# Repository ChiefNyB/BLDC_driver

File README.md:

# BLDC driver
 [TI DRV10983-Q1](https://www.ti.com/product/DRV10983-Q1/) based BLDC motor controller

 Development software: KiCad 8.0.5 (latest)

 ## *Üzenet*

 Szerintem majd ide a README-be írogathatjuk dokumnetáció vázlatos részét,
 a számítást meg Excelbe vagy valami python scriptbe lehet nyomni
 (ugyanígy version controllozva), aztán innen aztán mehet majd Word-be a bővebb leírás.

 Éés szerintem nyugodtan írogathatunk ide kommenteket is, talán kevésbé veszik
 el mint a chatben.

 Légyszi nézzétek meg a katalógust is (bent van a datasheet mappában), meg az áramkört is,
 igyekeztem leírni a dolgokat amiket csináltam. Mindezek alapján remélem, hogy nektek is érthető lesz majd, hogy mi mit csinál.
 Ha bármi kérdésetek van, írjátok akár ide valahova, akár messengeren. Légyszi mindketten olvassátok el az egész README-t!
 Köszi :)

 Ide kigyűjtöttem, hogy szerintem még mi kell:

 ## További lépések (nagy vonalakban)

  - Komponensek értékeinek kiszámítása --> komponensek választása
  - Fizikai layout kialakítása
  - (adhatnánk majd a hozzá passzoló motorokra egy példát)

## Dokumentáció vázlatosan (kapcsolás)
(ömlesztett gondolatok, egy csöppet össze-vissza)

KORREKCIÓ: A TVS DIÓDÁT EGYENLŐRE KISZEDTEM, VAN BEÉPÍTETT A CHIPBE
  
  - a chip modellt (footprint, stb...) a
  TI-os lapról töltöttem és illesztettem be: [link](https://vendor.ultralibrarian.com/TI/embedded/?gpn=DRV10983-Q1&package=PWP&pin=24&sid=&c=0)
  (lementettem saját global libraryba... ha nektek valami miatt nem látszódna, akkor
  ezt lehet nektek is meg kell csinálni)
  - IC bekötése a datasheet 64. oldalán található 71.figureban, egy csomó komponens (főleg kondik) értéke innen van
  található kapcsolás alapján (lehet arról írni esetleg, hogy milyen funkciói vannak
  az IC-nek)
    - 12Vról megy, (esetleg 24V, de ha 28-ig visszatölt, akkor már egyébként lekapcsolja a powerstaget)
    - I2C max 400kHz
    - milyen lekapcsolási-biztonsági funkciók vannak (Over voltage, o.current, thermal shutdown...)
  - a schematic hierarhikus, több lapból áll (drive, power), de nem is biztos hogy szükség lenne rá, mert elég egyszerű,
  csak kicsit fancybb és esetleg segíti a logikát átlátni
  - a pontos típus: [DRV10983SQ](https://www.ti.com/product/DRV10983-Q1/part-details/DRV10983SQPWPRQ1) legyen, ha standby modeban is 
  használni szeretnénk az 5V-os buck convertert --> mikrovezérlő meghajtható róla (ld. katalógus 3.o.)
  - I2C védelmet és szűrést [ez](https://www.we-online.com/components/media/o734709v410%20ANP121a%20%20Filter%20and%20surge%20protection%20for%20I2C%20Bus%20EN.pdf)
  alapján csináltam --> itt javasolt komponensekkel (ferrit gyöngy és TVS dióda) megegyező paraméterűeket lesz majd érdemes választani
  (egyenlőre egy kb hasonlót raktam be)
  - terveim szerint csinálok 2 verziót:
    - csatlakozós (Táp & motor is csatlakozós)
    - beforrasztós (táp& motornak csak pad-ek vannak amikre majd rá lehet forrasztani a vezetékeket)
    (ez az ahol a testpoint (TP) nevű kivezetések vannak)
  - a TI IC alatt a túloldalon van egy PAD (majd thermal viákkal összekötve) a GND-hez kötve, hogy hőt disszipáljon
  és ide lehet(ne) rakni majd a hűtőbordát is
  - van egy sima GND és egy PWRGND, hogy a motor áramai minél kevésbé zavarjanak bele a digitális jelekbe, ezek össze vannak kötve egy 0ohmos ellenállással
  - az 5V (output) jelenlétét LED jelzi
  - decoupling capacitorok közel az IC-hez (majd a kialakításnál fizikailag)
  - minden jel-bemenet és kimenet, ami ki van vezetve (SCL, SDA, FG, SPEED, DIR) 3V3 TVS diódával védve ESD ellen
  - I2C csak 3V3 szinten mehet
  - FG pin 3V3-as impulzusokat ad (to be checked in datasheet)
  - DIR és SPEED bemeneten használható 5V-os jel (azaz megtáplálható egy sima potiról és kapcsolóról, ennek az egy panelnek a segítségével)
    - viszont ehhez előbb I2C-n be kell konfigurálni
    - a bemenetek egy-egy feszültségosztóval le vannak skálázva 3v3-ra
    - ehhez majd lesznek számítások, poti értéke
  - a legvégén esetleg kérhetünk majd árajánlatot ha unatkozunk :P

  - az I2C-t úgy lehet használni, ha a külső áramkör GND-je össze van kötve a motordriver GND_D-jével
  - az 5V-os bemenet használatához is legalább a GND-t kell bekötni

  ## Szükséges számítások, paraméterek
  Légyszi Kristóf ide, vagy valami fileba majd gyűjtsd ki a komponens nevét/számát (pl.: R1) és a linket hogy melyiket választottuk...
  Majd belepakkolom a schematicba és generálok belőle egy BOM .csv filet.
  ( Lehetséges oldalak: farnell, rs-online, lomex, TME ...ilyesmik. Csak legyen magyar oldal! )
  (Esetleg lehet egy specifikus motor amit kinézünk, és annak a pramaétereit is felhasználjuk a számításokhoz)

  - elsősorban a TI-os katalógus alapján, a typical application résznél van egy lista hogy ők mit javasolnak
  - csak SMD alkatrészeket please
  - alapból ilyen 0603-as (mármint inches 0603, mert a metrikus méretek el vannak tolva) méretű ellenállásokat és kondikat stb. keresünk,
  esetleg kicsit kisebb vagy nagyobb (de nyilván ha nagyobb kell, akkor nagyobb kell, pl valszeg a táp kondija az gyanús, hogy nagyobb)
    - ellenállás választásnál ki kell számolni a teljesítményét és aszerint kell választani (0.25W; 1W ...)
    - LED-nél választani kell egy LED-et, majd az ahhoz előírt mA-hez választunk egy ellenállást, a színét rád bízom Kristóf ;)
    - kondiknál a feszültséget és a kapacitást kell nézni alapból
    - SPEED és DIR inputokra olyan feszültségosztó kell (ellenállásértékek), amik leskálázzák a bejövő 5V-ot 3,3-ra
  - I2C védelem: ld. dokumentáció vázlatpontjai közt, illetve ezek alapján még újra számíthatók a felhúzó ellenállások értékei is
  - ha nagyon fancy-k akarunk lenni, egy thermal calculationt is nyomhatunk és esetleg egy hűtőbordát is válasszunk (1. gyakorlat -> pdf kb. 10. oldal)
  - TVS diódák kapcsolása nem látszik a kapcs rajzon de az assets mappában megtalálható

  ## Kiválasztott alkatrészek
  Feltöltöttem egy Excel táblában a katalógusokból kiválasztott áramköri elemeket. A dokumentációhoz ideírom, amit csináltam:

  - Katalógusból kiválasztottam az ajánlások miatt előre ismert áramköri elemeket + a LED-et
  - Három kis számolás volt:
    - LED ellenállás,
    - feszültségosztók (TI online számolójával: [link](https://www.ti.com/download/kbase/volt/volt_div3.htm)),
    - I2C felhúzó ellenállások min-max értékeinek újraszámolása (az ajánlottak jók maradtak).

  Minden számolás és az összes alkatrész az Excelben. Alkatrészekhez van típuszsám, link, footprint adat és méretezési feltétel is (ha volt).
  A termikus számítások nem voltak kivitelezhetők, nincs elég adat veszteségekre vagy case-sink hőellenállásra (vagy hogy egyáltalán becsüljük).
  Elvileg a driver alá kerülő thermal pad elegendő, bele lehet írni a dokumentációba, hogy igény szerint lehet még adni hozzá.

  ## PCB alias NYÁK design
  - csatolásmentesítő kondik közel az IC-hez, mindegyiknek saját viája van a GND-hez
  - 45°-os track törésszögek a jelreflexió elkerülésére
  - thermal via-k: 20mil hole diameter, 8mil hole (for least resistance) ahogy [itt](https://www.ti.com/lit/an/slva959b/slva959b.pdf) a 2.5-ben írják
  - a teljesítményfolyamban lévő track-ek és viák méretezve vannak (viából van egy dupla is, bár nem feltétlen lenne rá szükség) 
  a számításokról készített screenshot az assetsben
  - digitális <--> teljesítény oldalak elválasztása fizikailag amennyire lehet
  - teljesítményvonalak kialakításánál fontos volt, hogy minél kisebb loopot csináljanak és rövidek legyenek
  - GND és GNDPWR egy 0ohmos ellenállással (R4) összekötve: kis vezetékellenállású összeköttetés a bemeneti GND és a digitális jelek
  GND-je közt
  - buck konverter trackjei default értéken vannak, de van róla számítás hogy elég (assetsben)
  - a power bemenetek jelölve vannak, a csatlakozónál légyszi csinálj egy ábrát, ami "katalógusba" mehetne
  - két sarokban letörések...mert csak... :P 
  - M2.5-ös mounting holeok hogy lehessen odacsavarozni valahova
  - az alsó oldalra ragasztható heatsink ha akarja a felhasználó, de figyelni kell,
  hogy ezen a részen galvanikus kapcsolat ne alakuljon ki a külvilággal
  - földkiöntés a sima GND-vel
  (- esetleg át lehetne alakítani hogy a heatsink-pad a sima GND-hez kapcsolódjon és a PWRGND-t másmerre vezetni, ha van idő...)
  - ... és ezeken kívül bármi amit látsz a boardon és érdemes leírni

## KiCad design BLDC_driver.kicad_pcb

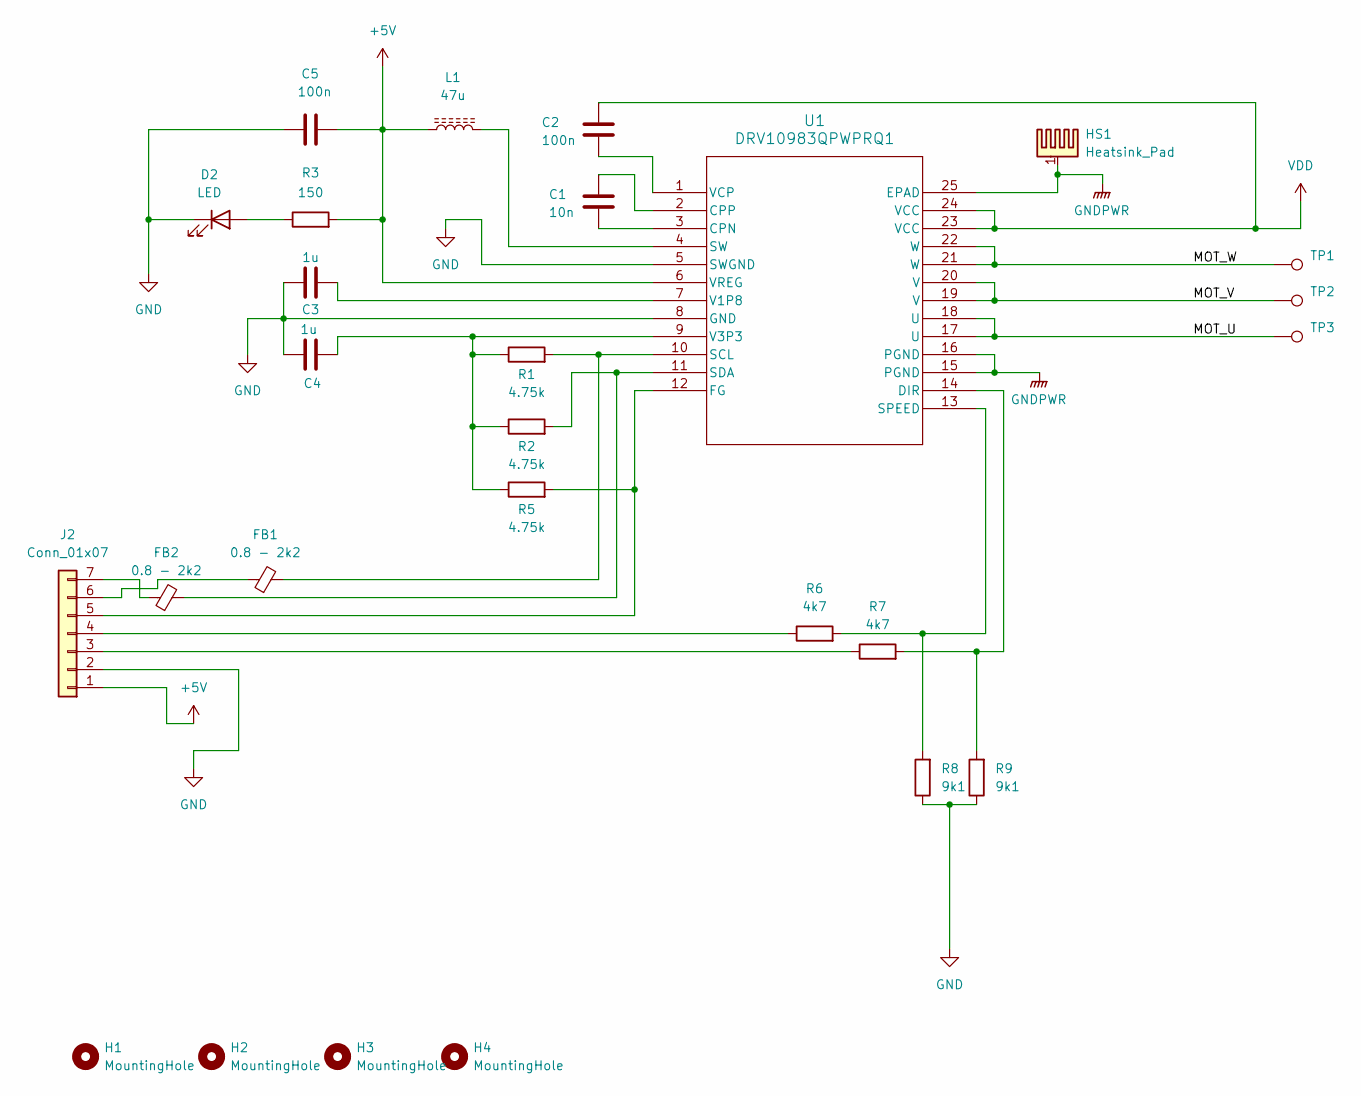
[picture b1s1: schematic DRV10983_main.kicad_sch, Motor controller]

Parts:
C1: 10n; C_0603_1608Metric
C2, C5: 100n; C_0603_1608Metric
C3, C4: 1u; C_0603_1608Metric
D2: LED; LED_0603_1608Metric
FB1, FB2: 0.8 - 2k2; L_0603_1608Metric
H1, H2, H3, H4: MountingHole; MountingHole_2.7mm_Pad
HS1: Heatsink_Pad; TestPoint_Pad_4.0x4.0mm
J2: Conn_01x07; JST_PH_S7B-PH-K_1x07_P2.00mm_Horizontal
L1: 47u; IND_VLS6045EX-470M
R1, R2, R5: 4.75k; R_0603_1608Metric
R3: 150; R_0603_1608Metric
R6, R7: 4k7; R_0603_1608Metric
R8, R9: 9k1; R_0603_1608Metric
TP1, TP2, TP3: TestPoint; TestPoint_Pad_3.0x3.0mm
U1: DRV10983QPWPRQ1; PWP24_2P4X5P16_TEX

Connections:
+5V: C5.2, J2.1, L1.1, R3.2, U1.6 (VREG)
/DRV IC/MOT_U: TP3.1, U1.17 (U), U1.18 (U)
/DRV IC/MOT_V: TP2.1, U1.19 (V), U1.20 (V)
/DRV IC/MOT_W: TP1.1, U1.21 (W), U1.22 (W)
GND: C3.1, C4.1, C5.1, D2.1 (K), J2.2, R8.1, R9.1, U1.5 (SWGND), U1.8 (GND); also elsewhere on the board
GNDPWR: HS1.1, U1.15 (PGND), U1.16 (PGND), U1.25 (EPAD); also elsewhere on the board
unnamed: D2.2 (A), R3.1
unnamed: J2.3, R7.1
unnamed: J2.4, R6.1
unnamed: J2.5, R5.2, U1.12 (FG)
unnamed: FB1.1, J2.6
unnamed: FB2.1, J2.7
unnamed: C1.2, U1.3 (CPN)
unnamed: C1.1, U1.2 (CPP)
unnamed: R7.2, R9.2, U1.14 (DIR)
unnamed: FB1.2, R1.2, U1.10 (SCL)
unnamed: FB2.2, R2.2, U1.11 (SDA)
unnamed: R6.2, R8.2, U1.13 (SPEED)
unnamed: L1.2, U1.4 (SW)
unnamed: C3.2, U1.7 (V1P8)
unnamed: C4.2, R1.1, R2.1, R5.1, U1.9 (V3P3)
unnamed: C2.2, U1.1 (VCP)
VDD: C2.1, U1.23 (VCC), U1.24 (VCC); also elsewhere on the board

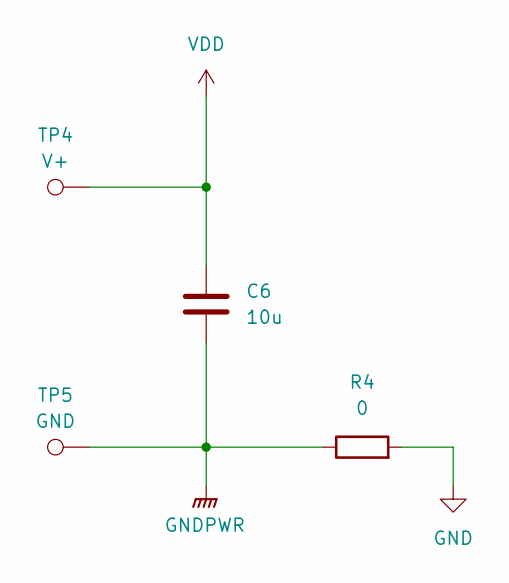
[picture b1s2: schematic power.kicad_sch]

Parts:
C6: 10u; C_0805_2012Metric
R4: 0; R_0603_1608Metric
TP4: V+; TestPoint_Pad_3.0x3.0mm
TP5: GND; TestPoint_Pad_3.0x3.0mm

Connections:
GND: R4.2; also elsewhere on the board
GNDPWR: C6.2, R4.1, TP5.1; also elsewhere on the board
VDD: C6.1, TP4.1; also elsewhere on the board

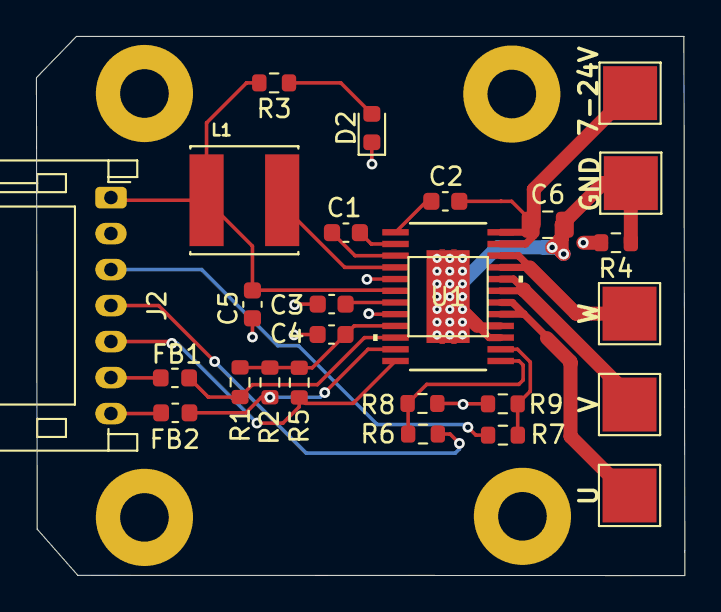
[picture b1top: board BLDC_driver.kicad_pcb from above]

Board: 2 copper layers, 36.0 x 29.9 mm, 31 parts (0 on the bottom side), 23 nets.

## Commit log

2024-10-11 Empty project added
2024-10-14 Driver schematic ready
2024-10-19 Schematic complete
    Completed power and controller sub-schematics, ESD protection
    Not completed: componenet values and footprints
    Not started: PCB layout design
2024-10-19 Update README.md
    minor corrections in README
2024-11-15 PCB v1 complete
    with images, README extended...
2024-11-17 Documantation added
2024-11-20 C6 capacitor reviewed
